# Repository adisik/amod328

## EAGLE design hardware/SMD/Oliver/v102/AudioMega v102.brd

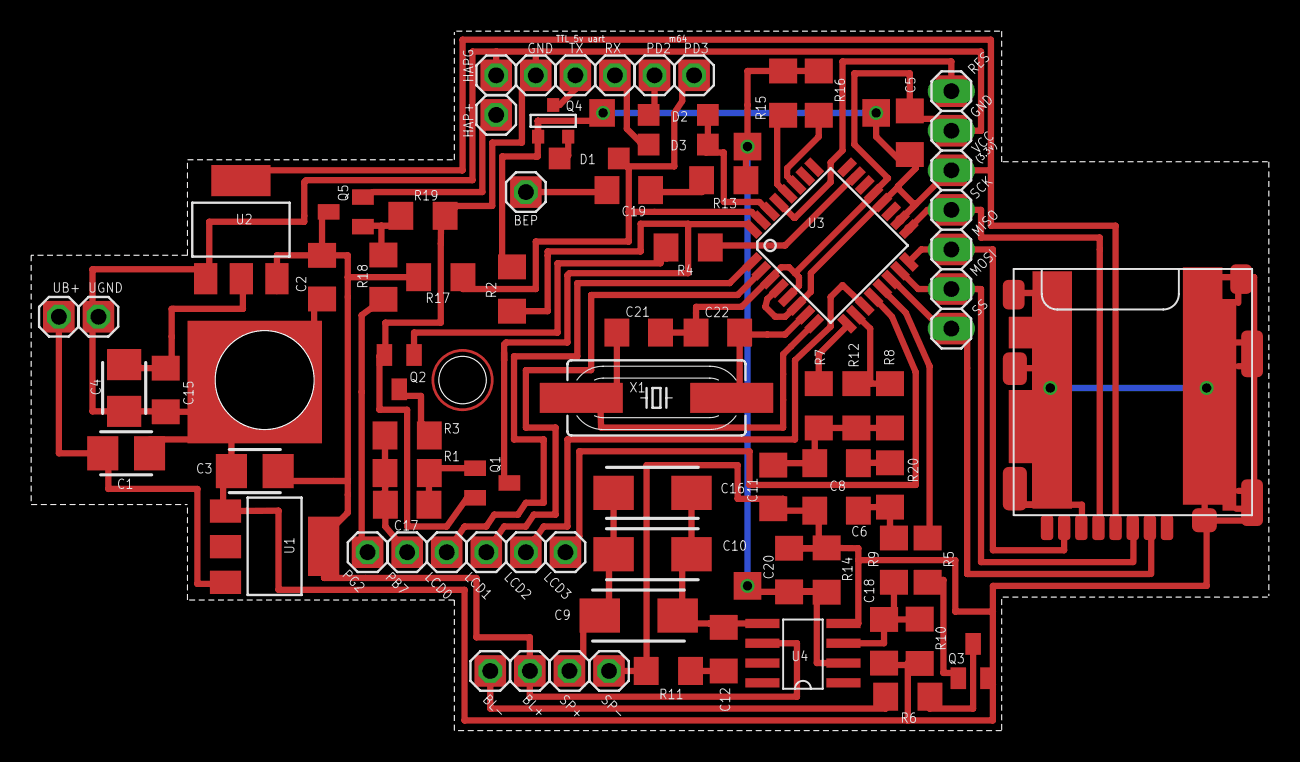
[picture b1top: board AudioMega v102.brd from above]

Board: 2 copper layers, 79.4 x 44.9 mm, 74 parts (0 on the bottom side), 48 nets.

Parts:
BEP: BEEPER; 1X01
BL+: BL+ (+5v); 1X01
BL-: BL-; 1X01
C1, C3, C4: 10uF; CT3528
C2, C5, C8, C15, C19: 100nF; C1206
C6: 330pf; C1206
C9, C10: 100uF; CT6032
C11: 22nF; C1206
C12, C20: 47nF; C1206
C16: 47uF; CT6032
C17: 10pF; C1206
C18: 4n7; C1206
C21, C22: 22pF; C1206
D1, D2, D3: BAT42; SOD123
GND: GND; 1X01
HAP+: Haptic; 1X01
HAPG: HapGND; 1X01
J1: 1X07
LCD0: D0; 1X01
LCD1: D1; 1X01
LCD2: D2; 1X01
LCD3: D3; 1X01
PB7: PB7; 1X01
PD2: PD2; 1X01
PD3: PD3; 1X01
PG2: PG2; 1X01
Q1, Q2, Q3, Q5: BC846ASMD; SOT23
Q4: 2N7002; SOT-23
R1, R13: 100k; R1206
R2, R4, R5, R17: 10k; R1206
R3, R15: 2k2; R1206
R6: 150; R1206
R7, R14, R16, R19: 1k; R1206
R8: 560k; R1206
R9, R20: 47k; R1206
R10: 4k7; R1206
R11: 10; R1206
R12: 470k; R1206
R18: 390; R1206
RX: TXD-TTL5v; 1X01
SP+: SP+; 1X01
SP-: SP-; 1X01
TX: RXD-TTL5v; 1X01
U1: REG1117-5; SOT223
U2: REG1117-3.3; SOT223
U3: ATMEGA328-AU; TQFP32-08
U4: LM386M; SO08
U$1: MICRO_SD_CONNECTOR
UB+: +Ub; 1X01
UGND: GND; 1X01
X1: 12MHz; HC49UP

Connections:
+5V: BL+.1, C2.1, C3.+, Q5.3, R17.2, U1.2, U1.4, U2.3, U4.6
B7: C17.2, PB7.1, R1.2, R3.2
CLK: Q1.3, R2.2, U3.32
GND: C1.-, C2.2, C3.-, C4.-, C5.2, C6.2, C11.2, C15.2, C18.2, C20.2, C21.1, C22.1, GND.1, HAPG.1, J1.6, Q1.2, Q2.2, Q3.2, R10.1, R11.1, R14.1, R19.2, SP-.1, U1.1, U2.1, U3.3, U3.5, U3.21, U4.4, UGND.1
unnamed: R4.1, U3.23
unnamed: HAP+.1, Q5.2
unnamed: J1.2, U3.15
unnamed: J1.3, U3.16
unnamed: J1.7, U3.29
unnamed: C22.2, U3.7, X1.2
unnamed: C21.2, U3.8, X1.1
unnamed: Q2.1, R4.2
unnamed: R16.1, U3.27
unnamed: R15.1, U3.28
unnamed: Q2.3, R3.1
unnamed: C17.1, Q1.1, R1.1
unnamed: C9.-, C10.-, C16.-, SP+.1
unnamed: C12.1, R11.2
unnamed: C9.+, C10.+, C12.2, C16.+, U4.5
unnamed: C18.1, R9.1, R10.2, U4.3
unnamed: BEP.1, C19.1
unnamed: C19.2, R13.1
unnamed: J1.1, U3.14
unnamed: C6.1, R9.2, R20.1
unnamed: C8.2, C11.1, R7.1, R8.1, R12.1
unnamed: Q3.3, R6.2
unnamed: R7.2, U3.9
unnamed: R8.2, R12.2, U3.10
unnamed: BL-.1, R6.1
unnamed: LCD3.1, U3.12
unnamed: LCD2.1, U3.11
unnamed: C1.+, U1.3, UB+.1
unnamed: Q3.1, R5.1
unnamed: R5.2, U3.13
unnamed: LCD1.1, U3.2
unnamed: LCD0.1, U3.1
unnamed: D3.C, RX.1
unnamed: D1.C, PD3.1, R17.1, U3.31
unnamed: D2.C, PD2.1
unnamed: PG2.1, R18.2
unnamed: Q4.1, TX.1
unnamed: D2.A, D3.A, U3.30
unnamed: Q5.1, R18.1, R19.1
unnamed: D1.A, Q4.2
unnamed: J1.4, U3.17
unnamed: C4.+, C5.1, C15.1, J1.5, Q4.3, R2.1, U2.2, U2.4, U3.4, U3.6, U3.18, U3.20
unnamed: C8.1, R20.2
VOL_B: C20.1, R13.2, R14.2, R15.2, R16.2, U4.2

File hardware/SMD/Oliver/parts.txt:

Partlist

Exported from AudioMega v101.brd at 27.11.2012 11:43:42

EAGLE Version 6.2.0 Copyright (c) 1988-2012 CadSoft

Assembly variant: 

Part     Value          Package   Library        Position (inch)       Orientation

C1       10uF           CT3528    resistor       (0.34 1.315)          R180
C2       100nF          C1206     resistor       (0.7 1.505)           R270
C3       10uF           CT3528    resistor       (0.58 1.315)          R0
C4       10uF           CT3528    resistor       (0.125 1.48)          R90
C5       100nF          C1206     resistor       (2.08 2.14)           R135
C8       100nF          C1206     resistor       (2.09 1.285)          R90
C9       100uF          CT6032    resistor       (1.355 0.94)          R0
C10      100uF          CT6032    resistor       (1.355 1.095)         R0
C11      47nF           C1206     resistor       (1.995 1.285)         R270
C12      47nF           C1206     resistor       (1.63 1.265)          R180
C15      100nF          C1206     resistor       (0.25 1.5)            R270
C16      47uF           CT6032    resistor       (1.355 1.25)          R0
C17      10pF           C1206     resistor       (0.97 1.74)           R90
C18      4n7            C1206     resistor       (2.065 0.875)         R270
C19      100nF          C1206     resistor       (1.575 0.92)          R90
C20      22nF           C1206     resistor       (1.94 1.135)          R0
C21      22pF           C1206     resistor       (1.405 1.655)         R180
C22      22pF           C1206     resistor       (1.625 1.655)         R0
D1       BAT42          SOD123    diode          (1.375 2.095)         R90
D2       BAT42          SOD123    diode          (1.6 2.095)           R270
D3       BAT42          SOD123    diode          (1.53 2.095)          R270
D4       BAT42          SOD123    diode          (1.445 2.095)         R90
J1                      1X07      pinhead        (2.235 1.965)         R90
JN1      0              R1206     resistor       (1.135 2.025)         R270
JP1      +Ub            1X01      pinhead        (0.16 1.28)           R0
JP2      GND            1X01      pinhead        (0.06 1.28)           R0
JP3      BL+ (+5v)      1X01      pinhead        (1.125 1.08)          R0
JP4      BL-            1X01      pinhead        (1.025 1.08)          R0
JP5      PB7            1X01      pinhead        (1.03 1.89)           R0
JP6      D0             1X01      pinhead        (0.93 1.89)           R0
JP7      D1             1X01      pinhead        (0.83 1.89)           R0
JP8      D2             1X01      pinhead        (0.73 1.89)           R0
JP9      D3             1X01      pinhead        (0.63 1.89)           R0
JP10     SP+            1X01      pinhead        (1.255 0.8)           R0
JP11     SP-            1X01      pinhead        (1.355 0.8)           R0
JP12     PD2            1X01      pinhead        (1.52 2.335)          R0
JP13     RXD-TTL5v      1X01      pinhead        (1.07 2.335)          R0
JP14     BEEPER         1X01      pinhead        (1.455 0.8)           R0
JP15     PD3            1X01      pinhead        (1.17 2.335)          R0
JP16     TXD-TTL5v      1X01      pinhead        (1.42 2.335)          R0
JP17     GND            1X01      pinhead        (1.62 2.335)          R0
Q1       BC846ASMD      SOT23     transistor-npn (0.99 1.52)           R180
Q2       BC846ASMD      SOT23     transistor-npn (1.36 1.88)           R90
Q3       BC846ASMD      SOT23     transistor-npn (2.29 1.33)           R0
Q4       2N7002         SOT-23    zetex          (1.175 2.21)          R180
Q5       2N7002         SOT-23    zetex          (1.3 2.33)            R90
R1       100k           R1206     resistor       (1.055 1.74)          R90
R2       10k            R1206     resistor       (1.295 2.095)         R270
R3       2k2            R1206     resistor       (1.19 1.865)          R180
R4       10k            R1206     resistor       (1.535 1.865)         R180
R5       10k            R1206     resistor       (2.28 1.505)          R90
R6       150            R1206     resistor       (2.28 1.135)          R90
R7       1k             R1206     resistor       (1.905 1.49)          R90
R8       560k           R1206     resistor       (2.09 1.49)           R90
R9       33k            R1206     resistor       (2.09 1.08)           R90
R10      4k7            R1206     resistor       (2.155 0.875)         R90
R11      10             R1206     resistor       (1.82 1.265)          R180
R12      470k           R1206     resistor       (1.995 1.49)          R90
R13      100k           R1206     resistor       (1.725 1.01)          R0
R14      1k             R1206     resistor       (1.94 1.01)           R180
R15      2k2            R1206     resistor       (1.79 2.185)          R180
R16      1k             R1206     resistor       (1.79 2.28)           R180
R17      1k             R1206     resistor       (1.06 2.17)           R90
U1       REG1117-5      SOT223    burr-brown     (0.64 1.11)           R270
U2       REG1117-3.3    SOT223    burr-brown     (0.44 1.915)          R0
U3       ATMEGA328-AU   TQFP32-08 atmel          (1.93 1.875)          R45
U4       LM386M         SO08      linear         (1.86 0.845)          R90
X1       12MHz          HC49UP    crystal        (1.465 1.49)          R0

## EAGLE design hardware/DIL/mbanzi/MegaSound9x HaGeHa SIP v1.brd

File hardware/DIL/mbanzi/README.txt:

The dimensions on this PCB have not been validated yet! Use this board at your own risk until I have tried a prototype in a 9x transmitter.

Thanks!
Mbanzi

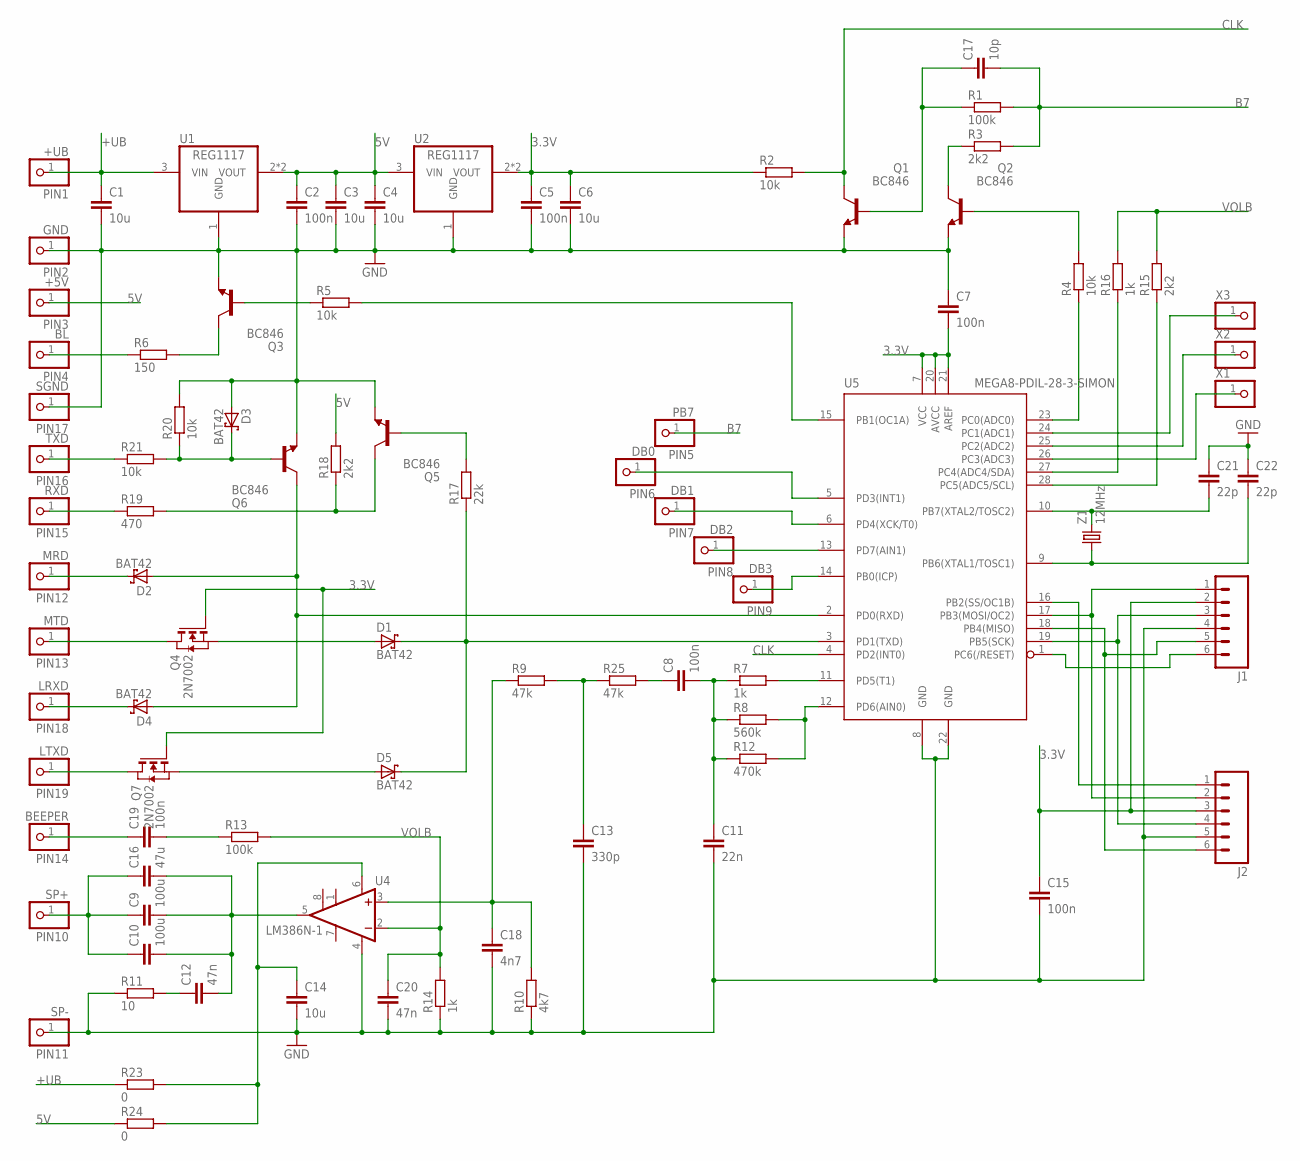
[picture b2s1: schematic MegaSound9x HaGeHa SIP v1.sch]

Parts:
+5V: PIN3; 1X01
+UB: PIN1; 1X01
BEEPER: PIN14; 1X01
BL: PIN4; 1X01
C1, C3, C4, C6, C14: 10u; C1206
C2, C5, C7, C8, C15, C19: 100n; C1206
C9, C10: 100u; C1206
C11: 22n; C1206
C12, C20: 47n; C1206
C13: 330p; C1206
C16: 47u; C1206
C17: 10p; C1206
C18: 4n7; C1206
C21, C22: 22p; C1206
D1, D2, D3, D4, D5: BAT42; SOD123
DB0: PIN6; 1X01
DB1: PIN7; 1X01
DB2: PIN8; 1X01
DB3: PIN9; 1X01
GND: PIN2; 1X01
J1, J2: M06SIP; 1X06
LRXD: PIN18; 1X01
LTXD: PIN19; 1X01
MRD: PIN12; 1X01
MTD: PIN13; 1X01
PB7: PIN5; 1X01
Q1, Q2, Q3, Q5, Q6: BC846; SOT23
Q4, Q7: 2N7002; SOT-23
R1, R13: 100k; R1206
R2, R4, R5, R20, R21: 10k; R1206
R3, R15, R18: 2k2; R1206
R6: 150; R1206
R7, R14, R16: 1k; R1206
R8: 560k; R1206
R9, R25: 47k; R1206
R10: 4k7; R1206
R11: 10; R1206
R12: 470k; R1206
R17: 22k; R1206
R19: 470; R1206
R23, R24: 0; R1206
RXD: PIN15; 1X01
SGND: PIN17; 1X01
SP+: PIN10; 1X01
SP-: PIN11; 1X01
TXD: PIN16; 1X01
U1: REG1117; SOT223
U2: REG1117; SOT223; MPN REG1117
U4: LM386N-1; DIL08
U5: MEGA8-PDIL-28-3-SIMON; DIL28-3-SIMON
X1, X2, X3: PINHD-1X1; 1X01
Z1: 12MHz; HC49US

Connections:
3.3V: C5.1, C6.1, C7.2, C15.1, J1.2, J2.3, Q4.3 (G), Q7.3 (G), R2.1, U2.2 (VOUT), U2.4 (VOUT), U5.7 (VCC), U5.20 (AVCC), U5.21 (AREF)
5V: +5V.1, C2.1, C3.1, C4.1, R18.2, R24.1, U1.2 (VOUT), U1.4 (VOUT), U2.3 (VIN)
+UB: +UB.1, C1.1, R23.1, U1.3 (VIN)
B7: C17.2, PB7.1, R1.2, R3.2
CLK: Q1.3 (C), R2.2, U5.4 (PD2(INT0))
D0: DB0.1, U5.5 (PD3(INT1))
GND: C1.2, C2.2, C3.2, C4.2, C5.2, C6.2, C7.1, C11.2, C13.2, C14.2, C15.2, C18.2, C20.2, C21.1, C22.1, D3.A, GND.1, J1.4, J2.5, Q1.2 (E), Q2.2 (E), Q3.2 (E), Q5.2 (E), Q6.2 (E), R10.1, R11.1, R14.1, R20.2, SGND.1, SP-.1, U1.1 (GND), U2.1 (GND), U4.4 (GND), U5.8 (GND), U5.22 (GND)
unnamed: C18.1, R9.1, R10.2, U4.3 (+IN)
unnamed: C12.1, R11.2
unnamed: C14.1, R23.2, R24.2, U4.6 (VS)
unnamed: C9.2, C10.2, C12.2, C16.2, U4.5 (OUT)
unnamed: C9.1, C10.1, C16.1, SP+.1
unnamed: BEEPER.1, C19.1
unnamed: C19.2, R13.1
unnamed: LTXD.1, Q7.1 (D)
unnamed: D5.A, Q7.2 (S)
unnamed: D4.C, LRXD.1
unnamed: MTD.1, Q4.1 (D)
unnamed: D2.C, MRD.1
unnamed: R19.1, RXD.1
unnamed: R21.1, TXD.1
unnamed: BL.1, R6.1
unnamed: Q5.3 (C), R18.1, R19.2
unnamed: Q3.3 (C), R6.2
unnamed: Q3.1 (B), R5.1
unnamed: Q2.1 (B), R4.2
unnamed: D3.C, Q6.1 (B), R20.1, R21.2
unnamed: Q5.1 (B), R17.2
unnamed: D2.A, D4.A, Q6.3 (C), U5.2 (PD0(RXD))
unnamed: D1.C, D5.C, R17.1, U5.3 (PD1(TXD))
unnamed: D1.A, Q4.2 (S)
unnamed: R7.2, U5.11 (PD5(T1))
unnamed: C13.1, R9.2, R25.1
unnamed: C8.1, R25.2
unnamed: C8.2, C11.1, R7.1, R8.1, R12.1
unnamed: R8.2, R12.2, U5.12 (PD6(AIN0))
unnamed: DB3.1, U5.14 (PB0(ICP))
unnamed: DB2.1, U5.13 (PD7(AIN1))
unnamed: DB1.1, U5.6 (PD4(XCK/T0))
unnamed: Q2.3 (C), R3.1
unnamed: R5.2, U5.15 (PB1(OC1A))
unnamed: C17.1, Q1.1 (B), R1.1
unnamed: R4.1, U5.23 (PC0(ADC0))
unnamed: R16.1, U5.27 (PC4(ADC4/SDA))
unnamed: R15.1, U5.28 (PC5(ADC5/SCL))
unnamed: C21.2, U5.10 (PB7(XTAL2/TOSC2)), Z1.2
unnamed: C22.2, U5.9 (PB6(XTAL1/TOSC1)), Z1.1
unnamed: U5.24 (PC1(ADC1)), X3.1
unnamed: U5.25 (PC2(ADC2)), X2.1
unnamed: U5.26 (PC3(ADC3)), X1.1
unnamed: J1.3, J2.4, U5.19 (PB5(SCK))
unnamed: J1.5, J2.6, U5.18 (PB4(MISO))
unnamed: J1.6, U5.1 (PC6(/RESET))
unnamed: J1.1, J2.2, U5.17 (PB3(MOSI/OC2))
unnamed: J2.1, U5.16 (PB2(SS/OC1B))
VOLB: C20.1, R13.2, R14.2, R15.2, R16.2, U4.2 (-IN)

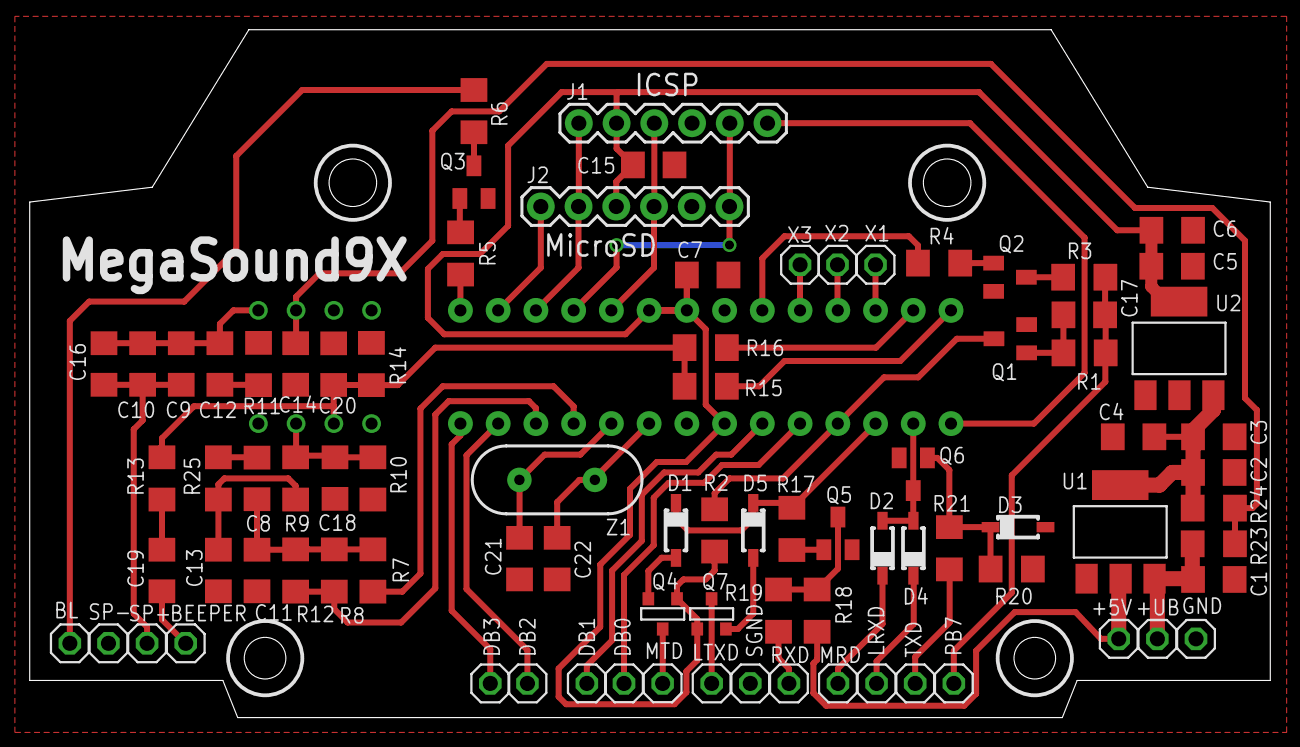
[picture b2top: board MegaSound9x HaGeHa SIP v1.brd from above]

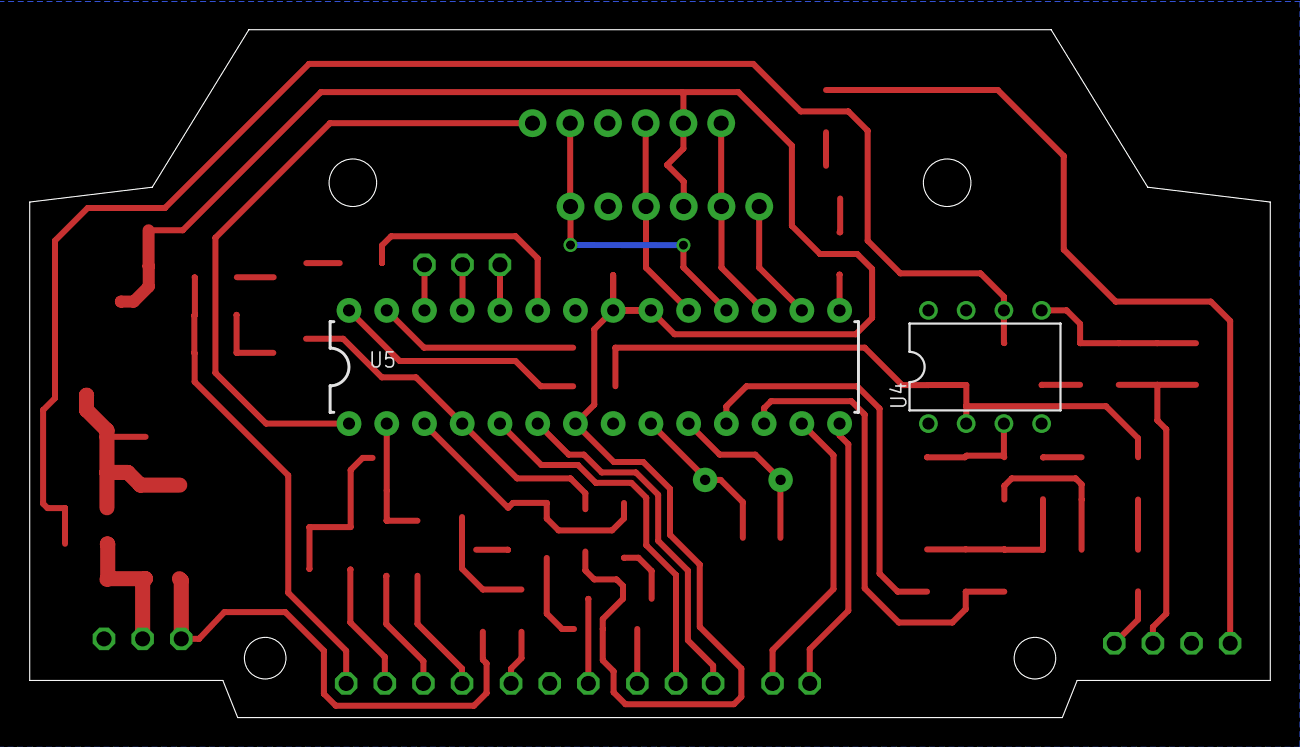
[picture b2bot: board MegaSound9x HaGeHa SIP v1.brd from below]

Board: 2 copper layers, 83.5 x 46.3 mm, 87 parts (2 on the bottom side), 56 nets.

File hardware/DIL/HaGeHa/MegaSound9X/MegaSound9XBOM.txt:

AudioMegaDIL2   Revised: Saturday, December 18, 2012					
          Revision: 02					
					
HaGeHa					
					
					
					
					
					
Bill Of Materials       December 8,2012      19:04:05	Page1				
					
Item	Quantity	Reference			Part		Type	
_______________________________________________________________________					
					
1	5		C1,C3,C4,C6,C14		10µF		sr1206	
2	6	C2,C5,C7,C8,C15,C19		100nF		sr1206	
3	2	C9,C10				100µF		sr1206	
4	1	C11				22nF		sr1206	
5	2	C12,C20				47nF		sr1206	
6	1	C13				330pF		sr1206	
7	1	C16				47µF		sr1206	
8	1	C17				10pF		sr1206	
9	1	C18				4n7		sr1206	
10	2	C21,C22				22pF		sr1206	
11	5	D1,D2,D3,D4,D5			BAT42		sr1206	
12	1	J1				ICSP		6sip100	
13	1	J2				MicroSD		6sip100	
14	5	Q1,Q2,Q3,Q5,Q6			BC846		sot123t	
15	2	Q4,Q7				2N7002		sot123t	
16	2	R1,R13				100k		sr1206	
17	5	R2,R4,R5,R20,R21			10k		sr1206	
18	3	R3,R15,R18			2k2		sr1206	
19	1	R6				150		sr1206	
20	3	R7,R14,R16			1k		sr1206	
21	1	R8				560k		sr1206	
22	2	R9,R25				47k		sr1206	
23	1	R10				4k7		sr1206	
24	1	R11				10		sr1206	
25	1	R12				470k		sr1206	
26	1	R17				22k		sr1206	
27	1	R19				470		sr1206	
28	2	R23,R24				0		sr1206	
29	1	U1				REG1117_5V	REG1117	
30	1	U2				REG1117_3.3V	REG1117	
31	1	U4				LM386		8dip300	
32	1	U5				ATMEGA328-DIL28	28dip300	
33	1	X1				12Mhz		x-tal

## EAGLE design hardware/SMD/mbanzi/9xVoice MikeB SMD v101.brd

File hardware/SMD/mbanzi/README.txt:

12/19/2012

Three designs in this directory:

9xVoice MikeB SMD v101:

This is an all SMD version of MikeB's 9xVoice board for the 9x, copied from 
images of his Eagle designs posted on 9xforums. You'll need to be pretty handy
with the soldering iron with this one, as all the chips are SMD too. This is 
likely the design I'll be building once MikeB has completed all his testing,
as I did the layout myself and therefore can only blame myself if it doesn't 
work.

AudioMega HaGeHa SMD v101:

This is a Eagle-ified, all SMD version of HaGeHa's AudioMega board for the 9x. 
I did not use the same pin layout as on the HaGeHa DIL design, as I was lazy 
and copied the MikeB SMD design! I did retain the 7 pin programmer & MicroSD 
layouts though. Again, you'll need to be pretty handy with the soldering iron 
with this one, as all the chips are SMD too.

AudioMega Oliver v101:

This is a slightly cleaned up, double sided version of Oliver's Eagle designed
AudioMega board he posted on 9xforums. Clearly Oliver also knows his stuff, as 
his original design is another masterpiece of PCB layout. I get double sided 
boards at no extra cost from my batching service, so I use 'em 'cause I can!

Eagle CAD Version: 6.3.0

Disclaimer: 

Although I confirmed that a printed version of MikeB & HaGeHa's PCBs fit 
perfectly in both my 9x transmitters, I have not actually etched & built the 
designs. I also have not checked Oliver's board, but a few 9xforums members have 
built the design, so it should be good. Feel free to modify the designs, but 
please let me know if you find any errors!

Notes:

The boards are double sided and use thru holes, so it may not be the best for 
home etching. I use a PCB batching service, oshpark.com (no affilliation) to
manufacture all my boards. It's as simple as uploading the Eagle .brd file,
wait 2 weeks or so and you get your boards. The only gotcha is that you need 
to order a minimum of 3 boards, so it may make sense to do a group order.

Thanks!
Mbanzi

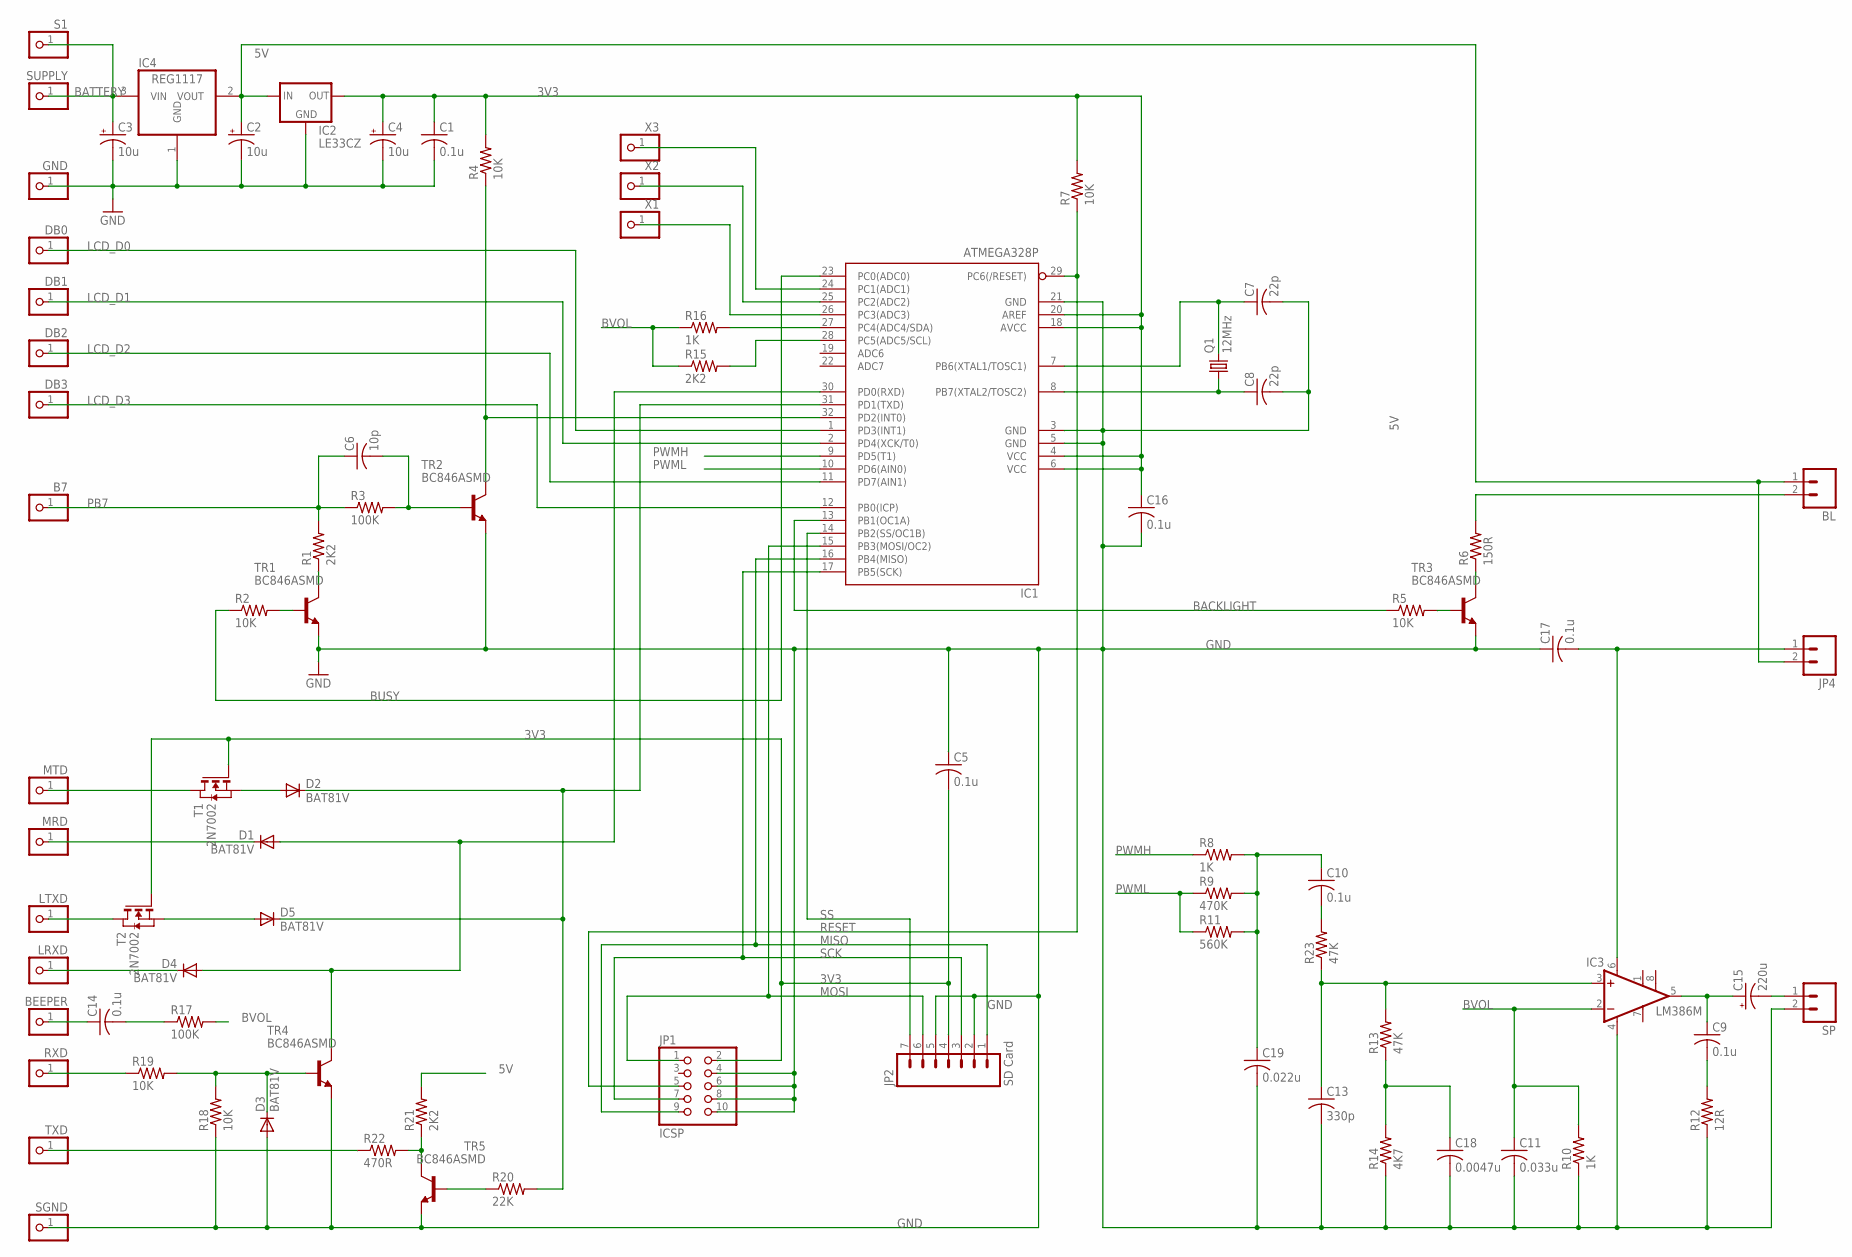
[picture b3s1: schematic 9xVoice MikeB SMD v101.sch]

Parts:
B7: PINHD-1X1; 1X01
BEEPER: PINHD-1X1; 1X01
BL: M02PTH; 1X02
C1, C5, C9, C10, C14, C16, C17: 0.1u; C1206
C2, C3, C4: 10u; A/3216-18R
C6: 10p; C1206
C7, C8: 22p; C1206
C11: 0.033u; C1206
C13: 330p; C1206
C15: 220u; CT7343
C18: 0.0047u; C1206
C19: 0.022u; C1206
D1, D2, D3, D4, D5: BAT81V; SOD123
DB0, DB1, DB2, DB3: PINHD-1X1; 1X01
GND: PINHD-1X1; 1X01
IC1: ATMEGA328P; TQFP32-08; MPN ATMEGA8-16AU
IC2: LE33CZ; SOT23
IC3: LM386M; SO08
IC4: REG1117; SOT223
JP1: ICSP; 2X05
JP2: SD Card; 1X07
JP4: M02PTH; 1X02
LRXD: PINHD-1X1; 1X01
LTXD: PINHD-1X1; 1X01
MRD: PINHD-1X1; 1X01
MTD: PINHD-1X1; 1X01
Q1: 12MHz; 2-SMD
R1, R15, R21: 2K2; R1206
R2, R4, R5, R7, R18, R19: 10K; R1206
R3, R17: 100K; R1206
R6: 150R; R1206
R8, R10, R16: 1K; R1206
R9: 470K; R1206
R11: 560K; R1206
R12: 12R; R1206
R13, R23: 47K; R1206
R14: 4K7; R1206
R20: 22K; R1206
R22: 470R; R1206
RXD: PINHD-1X1; 1X01
S1: PINHD-1X1; 1X01
SGND: PINHD-1X1; 1X01
SP: M02PTH; 1X02
SUPPLY: PINHD-1X1; 1X01
T1, T2: 2N7002; SOT-23
TR1, TR2, TR3, TR4, TR5: BC846ASMD; SOT23
TXD: PINHD-1X1; 1X01
X1, X2, X3: PINHD-1X1; 1X01

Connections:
3V3: C1.1, C4.+, C5.2, C16.1, IC1.4 (VCC), IC1.6 (VCC), IC1.18 (AVCC), IC1.20 (AREF), IC2.2 (OUT), JP1.2, JP2.4, R4.2, R7.2, T1.3 (G), T2.3 (G)
5V: BL.1, C2.+, IC2.3 (IN), IC4.2 (VOUT), JP4.2, R21.2
BACKLIGHT: IC1.13 (PB1(OC1A)), R5.1
BATTERY: C3.+, IC4.3 (VIN), S1.1, SUPPLY.1
BUSY: IC1.23 (PC0(ADC0)), R2.1
BVOL: C11.1, IC3.2 (-IN), R10.2, R15.1, R16.1, R17.2
GND: C1.2, C2.-, C3.-, C4.-, C5.1, C7.2, C8.2, C11.2, C13.2, C16.2, C17.1, C18.2, C19.2, D3.A, GND.1, IC1.3 (GND), IC1.5 (GND), IC1.21 (GND), IC2.1 (GND), IC3.4 (GND), IC4.1 (GND), JP1.4, JP1.6, JP1.8, JP1.10, JP2.2, JP2.5, R10.1, R12.1, R14.1, R18.1, SGND.1, SP.2, TR1.2 (E), TR2.2 (E), TR3.2 (E), TR4.2 (E), TR5.2 (E)
LCD_D0: DB0.1, IC1.1 (PD3(INT1))
LCD_D1: DB1.1, IC1.2 (PD4(XCK/T0))
LCD_D2: DB2.1, IC1.11 (PD7(AIN1))
LCD_D3: DB3.1, IC1.12 (PB0(ICP))
MISO: IC1.16 (PB4(MISO)), JP1.9, JP2.1
MOSI: IC1.15 (PB3(MOSI/OC2)), JP1.1, JP2.6
unnamed: R21.1, R22.2, TR5.3 (C)
unnamed: R22.1, TXD.1
unnamed: R20.1, TR5.1 (B)
unnamed: IC1.28 (PC5(ADC5/SCL)), R15.2
unnamed: IC1.27 (PC4(ADC4/SDA)), R16.2
unnamed: IC1.26 (PC3(ADC3)), X1.1
unnamed: IC1.25 (PC2(ADC2)), X2.1
unnamed: IC1.24 (PC1(ADC1)), X3.1
unnamed: R19.1, RXD.1
unnamed: D3.C, R18.2, R19.2, TR4.1 (B)
unnamed: D4.C, LRXD.1
unnamed: D5.A, T2.2 (S)
unnamed: D2.A, T1.2 (S)
unnamed: MTD.1, T1.1 (D)
unnamed: LTXD.1, T2.1 (D)
unnamed: D1.C, MRD.1
unnamed: R1.1, TR1.3 (C)
unnamed: R2.2, TR1.1 (B)
unnamed: C6.2, R3.2, TR2.1 (B)
unnamed: BEEPER.1, C14.1
unnamed: C14.2, R17.1
unnamed: R5.2, TR3.1 (B)
unnamed: R6.1, TR3.3 (C)
unnamed: C10.2, R23.2
unnamed: IC1.32 (PD2(INT0)), R4.1, TR2.3 (C)
unnamed: C8.1, IC1.8 (PB7(XTAL2/TOSC2)), Q1.P$1 (1)
unnamed: C7.1, IC1.7 (PB6(XTAL1/TOSC1)), Q1.P$2 (2)
unnamed: BL.2, R6.2
unnamed: C9.1, C15.+, IC3.5 (OUT)
unnamed: C9.2, R12.2
unnamed: C15.-, SP.1
unnamed: C17.2, IC3.6 (VS), JP4.1
unnamed: C13.1, IC3.3 (+IN), R13.2, R23.1
unnamed: C10.1, C19.1, R8.2, R9.2, R11.2
unnamed: C18.1, R13.1, R14.2
PB7: B7.1, C6.1, R1.2, R3.1
PWMH: IC1.9 (PD5(T1)), R8.1
PWML: IC1.10 (PD6(AIN0)), R9.1, R11.1
RESET: IC1.29 (PC6(/RESET)), JP1.5, R7.1
RXD: D1.A, D4.A, IC1.30 (PD0(RXD)), TR4.3 (C)
SCK: IC1.17 (PB5(SCK)), JP1.7, JP2.3
SS: IC1.14 (PB2(SS/OC1B)), JP2.7
TXD: D2.C, D5.C, IC1.31 (PD1(TXD)), R20.2

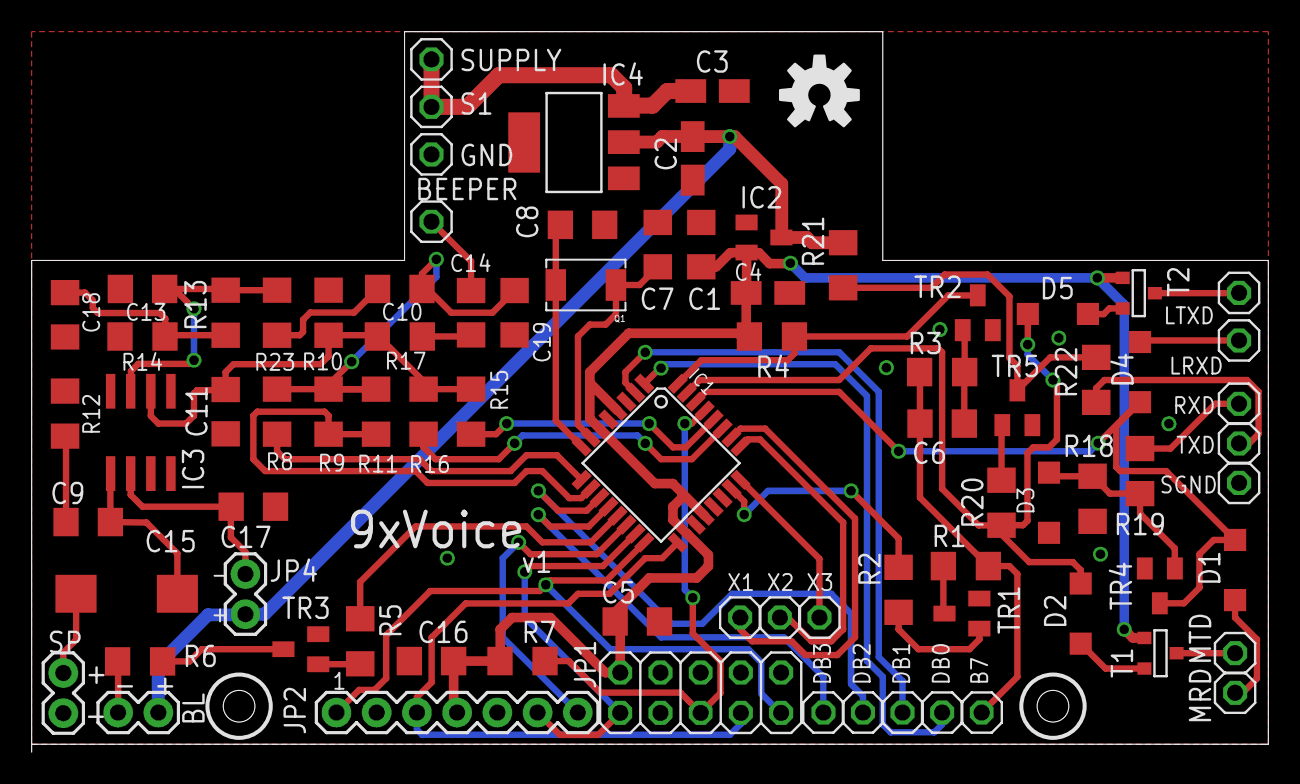
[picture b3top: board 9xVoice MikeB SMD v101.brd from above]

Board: 2 copper layers, 78.1 x 45.5 mm, 83 parts (0 on the bottom side), 56 nets.

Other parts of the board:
U$1: OSHW-LOGO-M

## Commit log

2012-10-24 Initial directory structure.
2012-10-30 12MHz version without volume control
2012-10-30 12MHz version. Have some debugging code
2012-10-30 no changes
2012-10-30 makefile
2012-10-31 + volume control
2012-10-31 -update
2012-10-31 - new version of DIR reading
2012-11-02 Documents about hardware for SMD design
2012-11-02 + beeper volume control
2012-11-06 zipped hex
2012-11-08 Bitmap from GERBER
2012-11-08 Placement
2012-11-08 scheme
2012-11-08 GERBER
2012-11-08 rename for fine
2012-11-08 ready_board
2012-11-08 changed amplifier gain with res&cap
2012-11-09 + mirrored image of board
2012-11-12 +Added Eagle files from mbanzi
2012-11-12 Updated: - Beeper connected to M64 (base of beeper transistor) - R10 changed to 33k - deleted some capasitors
2012-11-13 updated: - removed gain changes. - changed R09 to 33k. Beeper pin connected to M64 (base of beeper's transistor). So, beeper and transistor can be removed.
2012-11-13 Updated: Maked in corresponding of last hageha version. - changed R09, not r10, to 33k.
2012-11-13 + Fuse settings
2012-11-14 Created initial 1206 version of the PCB & renamed files
2012-11-16 Updated: - changes in audio_on(), audio_off() - PWM non stoped - compiling for atmega168, 12&16MHz
2012-11-27 new board from Hans
2012-11-27 new board from Hans. DIP micros, other SMD 1206
2012-11-27 add Oliver's board
2012-11-29 Add bootloader, Busy ON at start, Volume setting, Speed up, remove clicks/pops
2012-12-01 +add gerber from HaGeHa
2012-12-02 + added missing .brd file
2012-12-05 - fixed parts list: add "Comment" instead "Library"
2012-12-12 Added readme
2012-12-12 Add Eagle CAD schematic for MikeB's design
2012-12-12 Add DIL version of MikeB's design
2012-12-12 Add initial version of MikeB's design
2012-12-12 Cleaned up the Eagle files as some of the designs are outdated.
2012-12-13 +add .png image
2012-12-14 + rebuild '328 (12MHz & 16MHz) and '168 (12MHz & 16MHz) versions
2012-12-14 + updated fuses fo bootloader
2012-12-20 Added Eagle 6.3.0 files for all my versions of the designs
2013-01-18 Added #define for CPU freq Change uart&timer initialisation calculated from F_CPU Removed some old commented code Added DEBUG mode
2013-01-27 Add BOM
2013-01-27 Added correct 3.3v VREG
2013-01-27 Renamed BOMs
2013-01-28 Update component
2013-01-29 Add latest HaGeHa MegaSound9X design
2013-01-29 Updated HaGeHa Eagle files
2013-01-31 Created wiki page through web user interface.
2013-02-05 Added latest MikeB changes
2013-02-05 Updated components
2013-02-05 Changed value of R12
2013-02-07 create new version of board
2013-02-11 Add disable serial output
2013-02-11 Make TX disable work properly
2013-02-13 Edited wiki page MegaSound9x through web user interface.
2013-02-13 + rebuild bootloader for '168 (12MHz version)
2013-02-13 + rebuild '168 (12MHz version)
2013-02-14 + build TEST MODE for '168 (12MHz version)
2013-02-18 updated v102 board + added connector for haptic motor + added last schematic changes from MikeB (connection to M64) + added last audio filter changes (filtering PWM noise) from Mike and Hans
2013-02-19 updated v102 board - corrected BAT & GND pads
2013-02-26 updated v102 board - checked for Gerber export - add Gerber files
2013-02-26 updated v102 board - some minore changes for home etching
2013-03-18 - fixed error near Q3
2013-05-13 Changed marking R1, R3 in .brd
2013-05-23 Serial upload to SD card added
2013-05-24 Add the updated amod_last.hex
2013-05-24 Fix file transfer >32K
2013-05-25 Add fffconf.h
2013-06-04 Improve bootloader, include date-time in serial updates
2015-04-12 Update with backup/restore
2015-10-26 Migrating wiki contents from Google Code

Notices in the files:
parts and their libraries:
SparkFun-FreqCtrl: Licensing: CC v3.0 Share-Alike You are welcome to use this library for commercial purposes.
